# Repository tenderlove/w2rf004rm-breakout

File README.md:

# Breakout board for W2RF004RM

This is a breakout board for the W2RF004RM

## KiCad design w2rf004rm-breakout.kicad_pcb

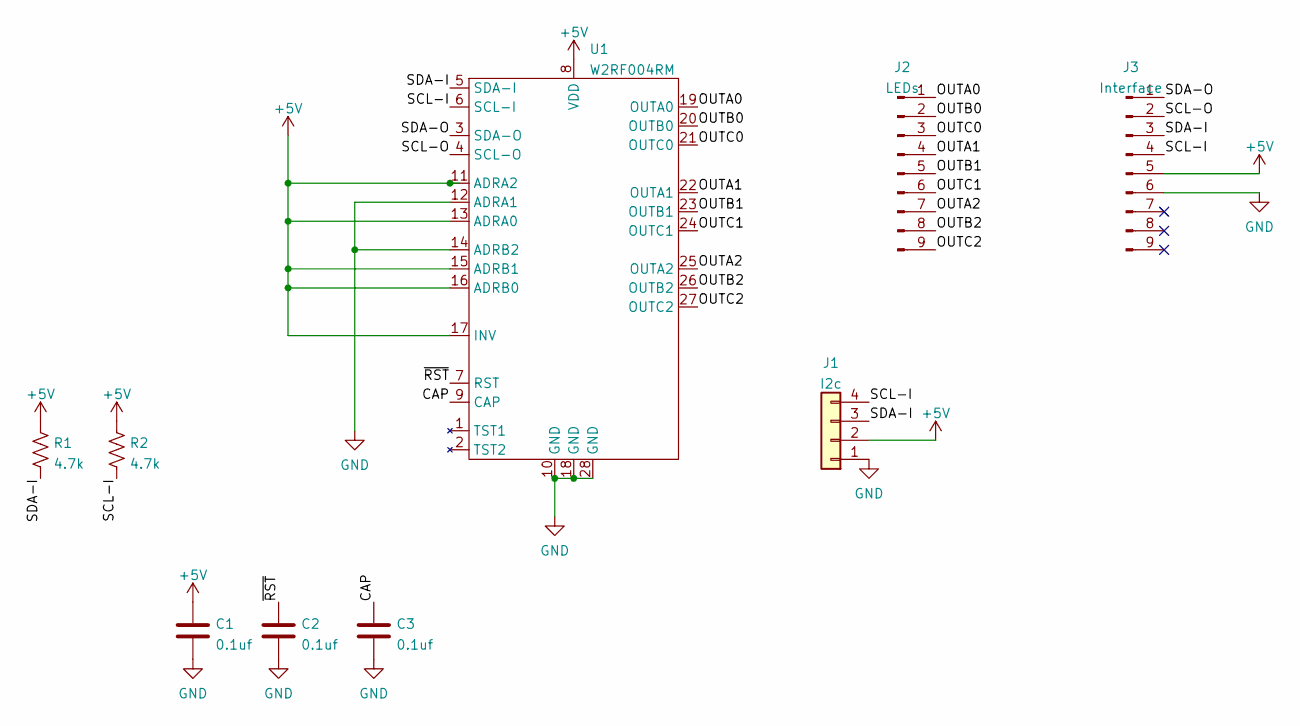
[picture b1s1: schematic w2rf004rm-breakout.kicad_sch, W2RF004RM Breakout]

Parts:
C1, C2, C3: 0.1uf; C_1206_3216Metric_Pad1.33x1.80mm_HandSolder
J1: I2c; JST_SH_BM04B-SRSS-TB_1x04-1MP_P1.00mm_Vertical
J2: LEDs; PinHeader_1x09_P2.54mm_Vertical
J3: Interface; PinHeader_1x09_P2.54mm_Vertical
R1, R2: 4.7k; R_1206_3216Metric_Pad1.30x1.75mm_HandSolder
U1: W2RF004RM; SSOP-28_5.3x10.2mm_P0.65mm

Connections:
+5V: C1.1, J1.2, J3.5, R1.1, R2.1, U1.8 (VDD), U1.11 (ADRA2), U1.13 (ADRA0), U1.15 (ADRB1), U1.16 (ADRB0), U1.17 (INV)
/CAP: C3.1, U1.9 (CAP)
/OUTA0: J2.1, U1.19 (OUTA0)
/OUTA1: J2.4, U1.22 (OUTA1)
/OUTA2: J2.7, U1.25 (OUTA2)
/OUTB0: J2.2, U1.20 (OUTB0)
/OUTB1: J2.5, U1.23 (OUTB1)
/OUTB2: J2.8, U1.26 (OUTB2)
/OUTC0: J2.3, U1.21 (OUTC0)
/OUTC1: J2.6, U1.24 (OUTC1)
/OUTC2: J2.9, U1.27 (OUTC2)
/SCL-I: J1.4, J3.4, R2.2, U1.6 (SCL-I)
/SCL-O: J3.2, U1.4 (SCL-O)
/SDA-I: J1.3, J3.3, R1.2, U1.5 (SDA-I)
/SDA-O: J3.1, U1.3 (SDA-O)
/~RST: C2.1, U1.7 (RST)
GND: C1.2, C2.2, C3.2, J1.1, J3.6, U1.10 (GND), U1.12 (ADRA1), U1.14 (ADRB2), U1.18 (GND), U1.28 (GND)

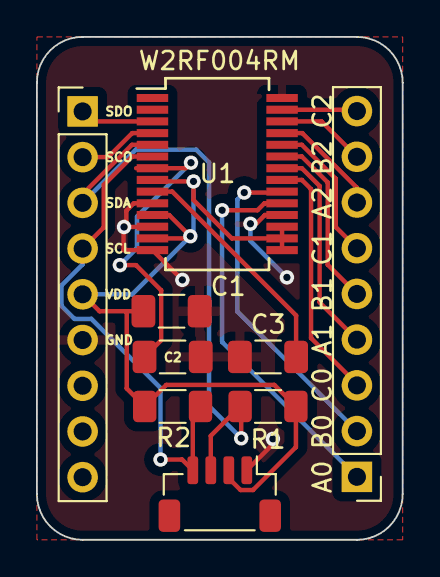
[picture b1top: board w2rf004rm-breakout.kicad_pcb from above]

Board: 2 copper layers, 20.3 x 27.9 mm, 9 parts (0 on the bottom side), 17 nets.

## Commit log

2022-02-06 initial

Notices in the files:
w2rf004rm-breakout.kicad_pcb:
CC BY 4.0
https://creativecommons.org/licenses/by/4.0
